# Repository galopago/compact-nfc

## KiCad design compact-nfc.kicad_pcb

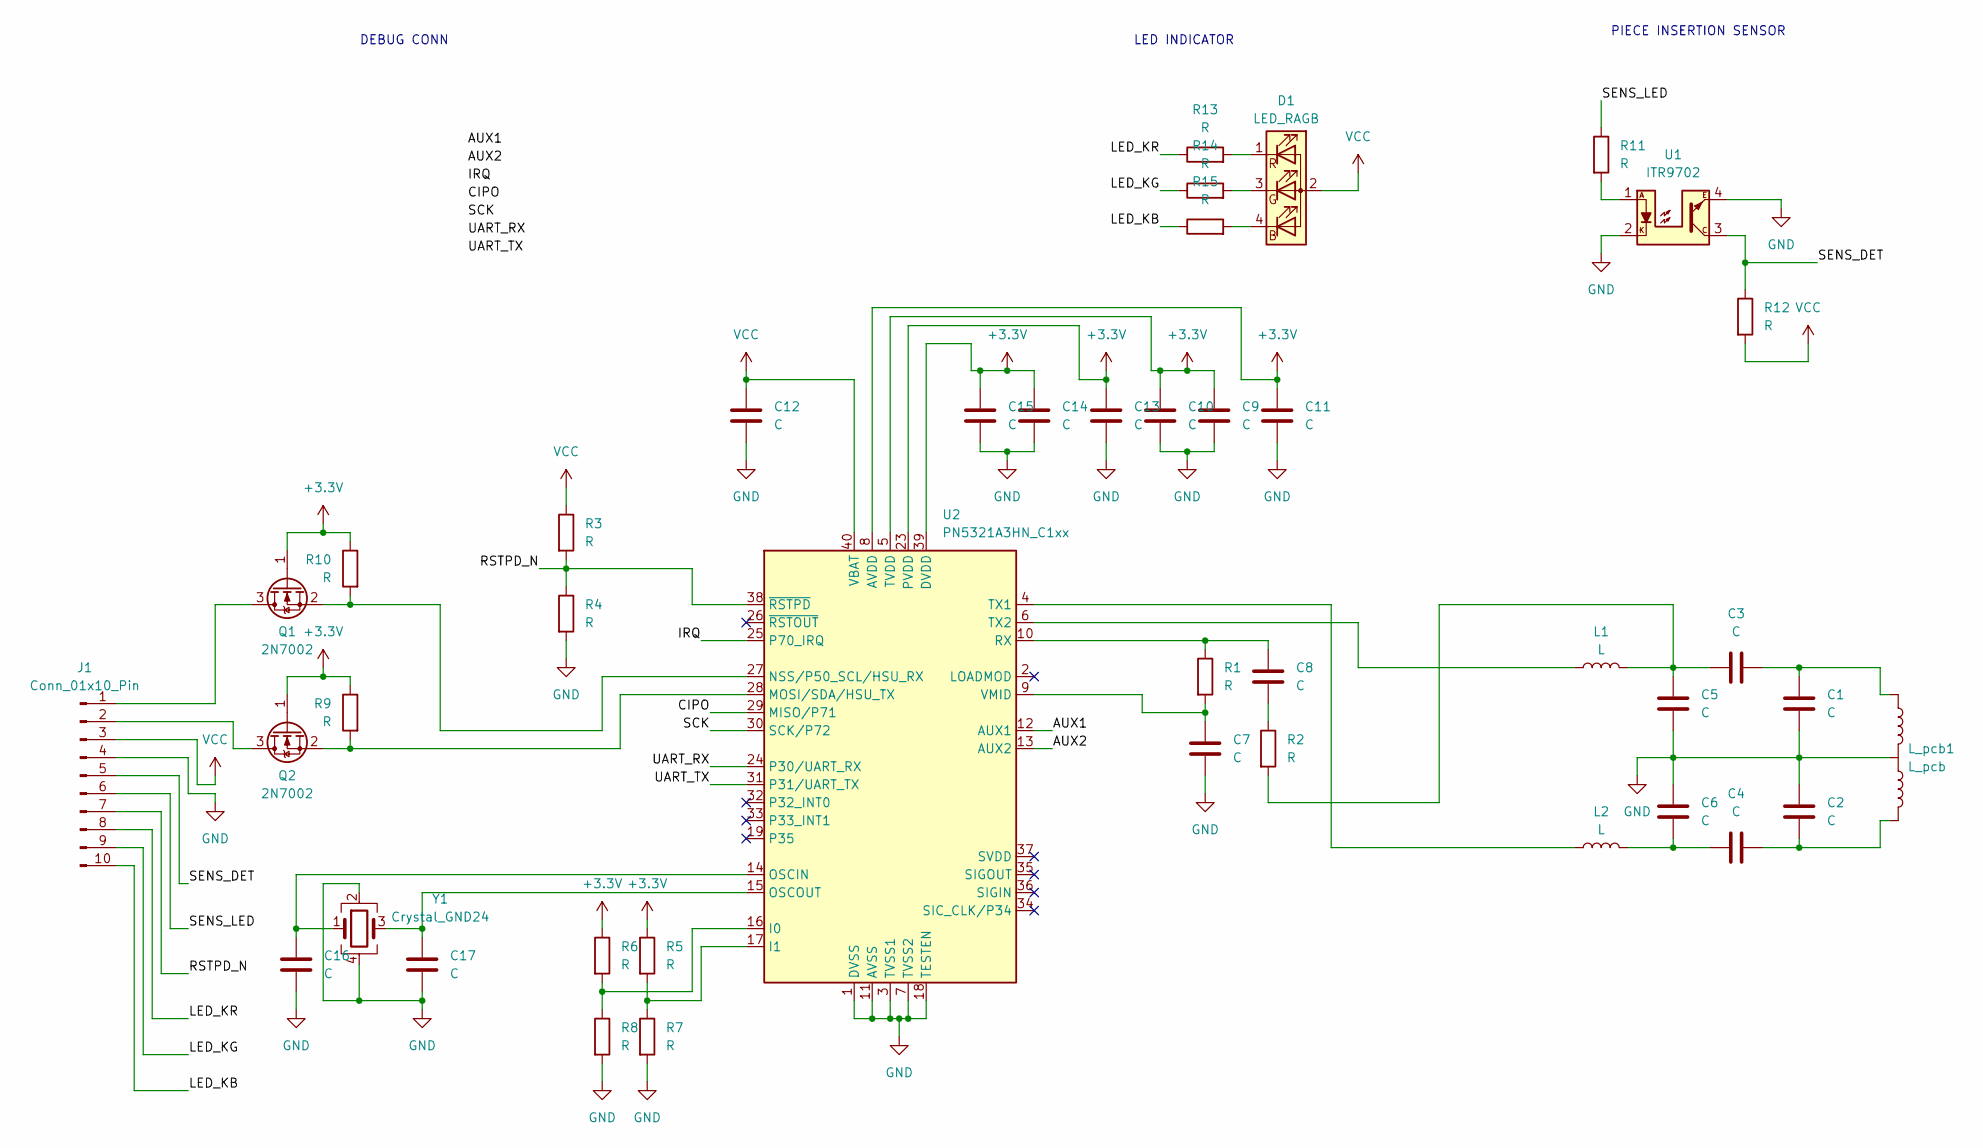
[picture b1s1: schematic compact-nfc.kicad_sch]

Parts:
C1, C2, C3, C4, C5, C6, C7, C8, C9, C10, C11, C12, C13, C14, C15, C16, C17: C; C_0805_2012Metric_Pad1.18x1.45mm_HandSolder
D1: LED_RAGB; LED_RGB_SMD_6028_2.8x3.5mm_Square
J1: Conn_01x10_Pin; PinHeader_1x10_P2.54mm_Vertical
L1, L2: L; L_1206_3216Metric_Pad1.22x1.90mm_HandSolder
L_pcb1: L_pcb; L_NFC_PCB
Q1, Q2: 2N7002; SOT-23
R1, R2, R3, R4, R5, R6, R7, R8, R9, R10, R11, R12, R13, R14, R15: R; R_0805_2012Metric_Pad1.20x1.40mm_HandSolder
U1: ITR9702; Everlight_ITR9702
U2: PN5321A3HN_C1xx; HVQFN-40-1EP_6x6mm_P0.5mm_EP4.1x4.1mm
Y1: Crystal_GND24; Crystal_SMD_3225-4Pin_3.2x2.5mm_HandSoldering

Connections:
+3.3V: C9.1, C10.1, C11.1, C13.1, C14.1, C15.1, Q1.1 (G), Q2.1 (G), R5.1, R6.1, R9.1, R10.1, U2.5 (TVDD), U2.8 (AVDD), U2.23 (PVDD), U2.39 (DVDD)
/AUX1: U2.12 (AUX1)
/AUX2: U2.13 (AUX2)
/CIPO: U2.29 (MISO/P71)
/IRQ: U2.25 (P70_IRQ)
/LED_KB: J1.10, R15.1
/LED_KG: J1.9, R14.1
/LED_KR: J1.8, R13.1
/RSTPD_N: J1.7, R3.2, R4.1, U2.38 (~RSTPD)
/SCK: U2.30 (SCK/P72)
/SENS_DET: J1.5, R12.1, U1.3
/SENS_LED: J1.6, R11.1
/UART_RX: U2.24 (P30/UART_RX)
/UART_TX: U2.31 (P31/UART_TX)
GND: C1.2, C2.1, C5.2, C6.1, C7.1, C9.2, C10.2, C11.2, C12.2, C13.2, C14.2, C15.2, C16.1, C17.1, J1.4, L_pcb1.2, R4.2, R7.2, R8.2, U1.2, U1.4, U2.1 (DVSS), U2.3 (TVSS1), U2.7 (TVSS2), U2.11 (AVSS), U2.18 (TESTEN), U2.41 (AVSS), Y1.2, Y1.4
unnamed: C1.1, C3.2, L_pcb1.1
unnamed: C2.2, C4.2, L_pcb1.3
unnamed: C3.1, C5.1, L1.2, R2.2
unnamed: C4.1, C6.2, L2.2
unnamed: C8.1, R2.1
unnamed: D1.4 (BK), R15.2
unnamed: D1.3 (GK), R14.2
unnamed: D1.1 (RK), R13.2
unnamed: J1.1, Q1.3 (D)
unnamed: J1.2, Q2.3 (D)
unnamed: Q1.2 (S), R10.2, U2.27 (NSS/P50_SCL/HSU_RX)
unnamed: Q2.2 (S), R9.2, U2.28 (MOSI/SDA/HSU_TX)
unnamed: R11.2, U1.1
unnamed: R6.2, R8.1, U2.16 (I0)
unnamed: R5.2, R7.1, U2.17 (I1)
unnamed: C16.2, U2.14 (OSCIN), Y1.1
unnamed: C17.2, U2.15 (OSCOUT), Y1.3
unnamed: C8.2, R1.1, U2.10 (RX)
unnamed: L2.1, U2.4 (TX1)
unnamed: L1.1, U2.6 (TX2)
unnamed: C7.2, R1.2, U2.9 (VMID)
VCC: C12.1, D1.2 (A), J1.3, R3.1, R12.2, U2.40 (VBAT)

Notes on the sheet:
LED INDICATOR
DEBUG CONN
PIECE INSERTION SENSOR

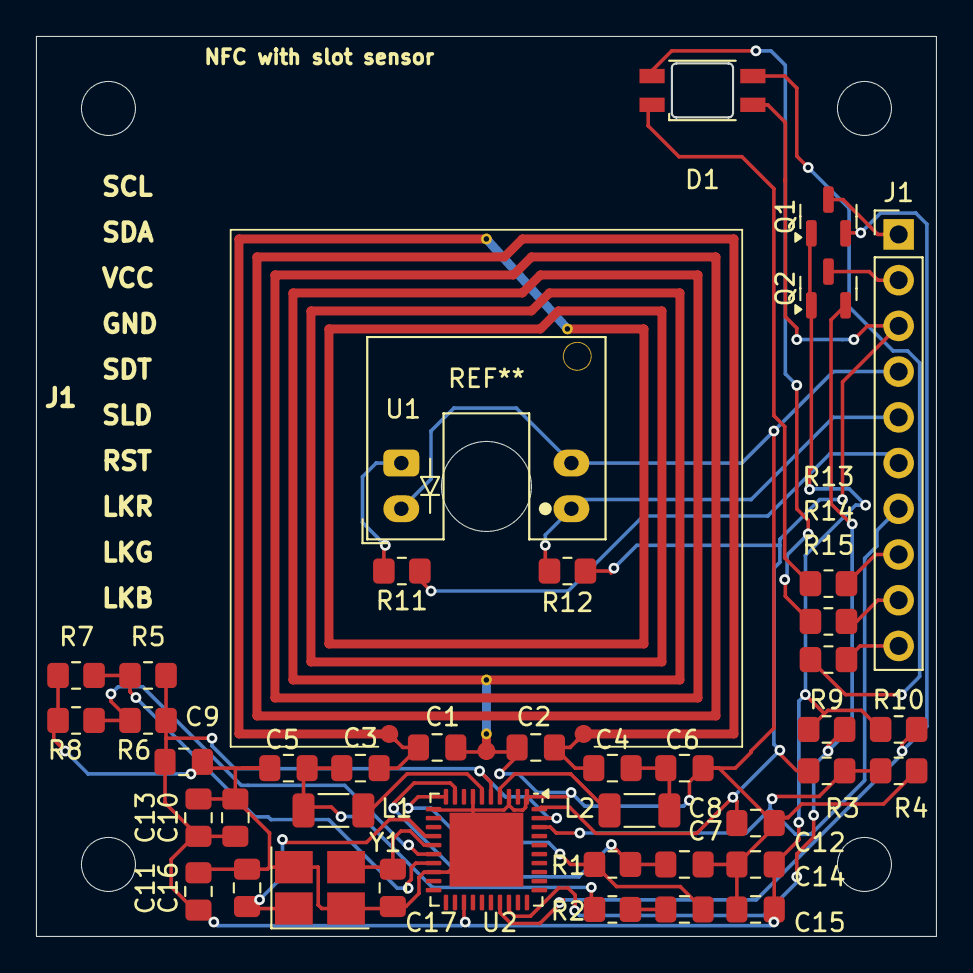
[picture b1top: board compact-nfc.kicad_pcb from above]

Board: 2 copper layers, 50.0 x 50.0 mm, 46 parts (0 on the bottom side), 30 nets.

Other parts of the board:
MH1, MH2, MH3, MH4: MountingHole_3mm

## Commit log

2026-01-06 Initial commit: KiCad project files
2026-01-06 Add infrared barrier sensor component: footprint and schematic symbol
2026-01-14 Add NFC chip and coil patterns for PCB
2026-01-16 Add coupling components to NFC antenna
2026-01-22 Update optical sensor fixation pin
    - Modify Everlight ITR9702 footprint (Everlight_ITR9702.kicad_mod)
    - Update PCB layout and schematic accordingly
2026-01-23 Add more components from reference schematic
2026-01-24 Start coil construction on PCB
2026-01-25 Add coil as PCB library component
    - Add L_NFC_PCB footprint (Inductor_PCB.pretty)
    - Add coil_pcb symbol
    - Update fp-lib-table and sym-lib-table
    - Update PCB and schematic with coil placement
2026-01-25 Add backup files and project backups
2026-01-25 Start clock crystal placement on PCB
2026-01-26 Add debug connector and start manual routing of critical RF coupling network sections
    - Added debug connector to schematic and PCB
    - Started manual routing of critical RF coupling network components
    - Updated footprint library table
2026-01-28 Complete main trace routing
    - Finished main trace routing for PCB layout
    - Updated schematic and project files
    - Updated backup files
2026-01-29 Organize silkscreen labels for component assembly identification
2026-01-30 Add Gerber files for single-card PCB
    Generated Gerber outputs for the compact NFC single-card PCB design,
    including copper layers, mask, paste, silkscreen, drill files and
    the single-board export zip.
2026-01-30 Fix silkscreen layer issues
    Silkscreen adjustments and corrections on the PCB design.
2026-01-30 Update panelized Gerber files
    Regenerated panel Gerber outputs for manufacturing.
